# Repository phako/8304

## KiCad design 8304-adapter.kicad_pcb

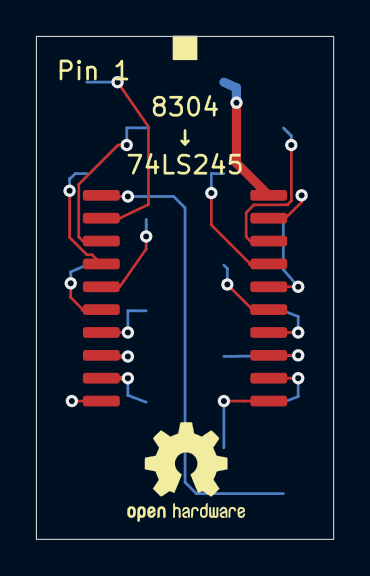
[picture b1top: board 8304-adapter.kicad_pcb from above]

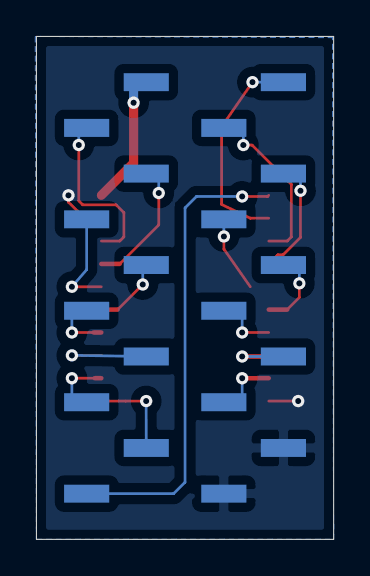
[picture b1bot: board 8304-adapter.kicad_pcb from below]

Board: 2 copper layers, 16.5 x 27.9 mm, 3 parts (2 on the bottom side), 19 nets.

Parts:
J2, J3: Conn_01x10; PinHeader_1x10_P2.54mm_Vertical_SMD_Pin1Right-nosilk
U1: 74LS245; SOIC-20W_7.5x12.8mm_P1.27mm-nosilk

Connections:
+5V: J3.1, U1.20
A0: J2.1, U1.2
A1: J2.2, U1.3
A2: J2.3, U1.4
A3: J2.4, U1.5
A4: J2.5, U1.6
A5: J2.6, U1.7
A6: J2.7, U1.8
A7: J2.8, U1.9
D0: J3.2, U1.18
D1: J3.3, U1.17
D2: J3.4, U1.16
D3: J3.5, U1.15
D4: J3.6, U1.14
D5: J3.7, U1.13
D6: J3.8, U1.12
D7: J3.9, U1.11
DIR: J3.10, U1.1
GND: J2.9, J2.10, U1.10, U1.19

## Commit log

2020-10-17 Initial import
2020-10-17 Remove accidental mail address copper
2020-10-18 Update layout to use SOIC version of 74LS245
2020-10-18 Minor fixes
